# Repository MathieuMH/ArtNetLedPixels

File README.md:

# ArtNetLedPixels
This is a small project to drive up to +4000 WS28xx LED pixels. It is made for a local free family festival called Copacobana. Which takes place in Ghent (Belgium) every year at the end of June.
As a light operator I like to experiment with budget friendly equipment (like WS28xx leds), to create nice moderate effects. Our club stage is mainly for the afterparty.
This project was used to illuminate the logo of the stage.
The board receives it data from a lighting desk, in our situation (Chamsys MQ500). We mainly use the Art-Net protocol since its quite easy to adopt. The output is driven with the FastLED library.

# Required Hardware
The setup consists of the following hardware:
* Teensy 3.1 or 3.2 (there is basicly no difference for this project)
* Wiznet Wiz850io (LAN tranceived based on the WIZ5000)
* Carrierboard (refer to the ArtNet_WS2812B folder, board is drawn in KiCad 5)

# Output
The board has 12 outputs with screw terminal and one with solder terminal at R14.

# Contributors
Mathieu (THIEU.Gent)
Copacobana Festival http://www.copacobana.be

# License
MIT License

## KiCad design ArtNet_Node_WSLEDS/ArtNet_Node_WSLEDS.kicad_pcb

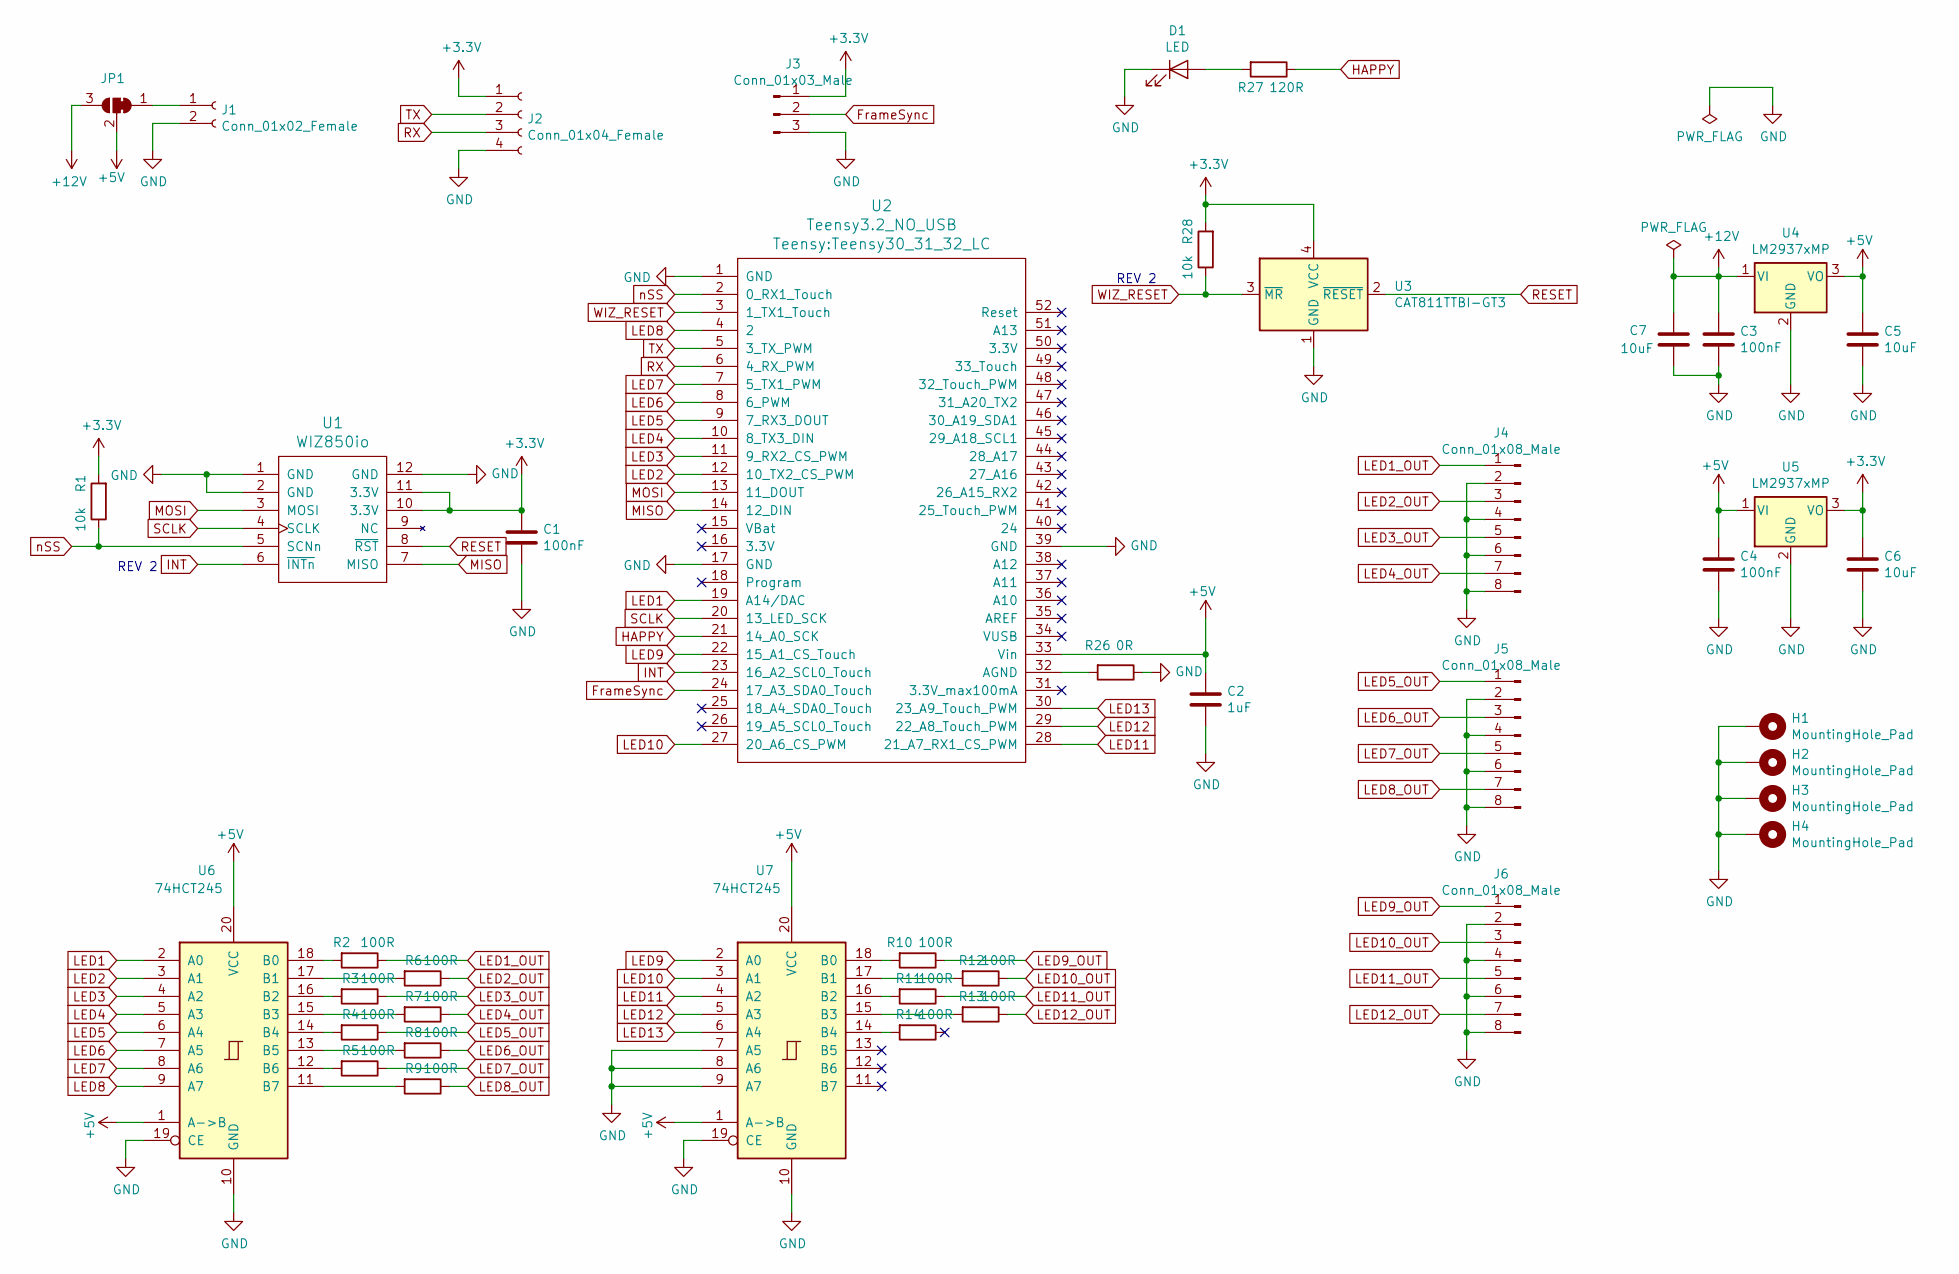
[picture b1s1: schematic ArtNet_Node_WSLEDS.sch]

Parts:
C1, C3, C4: 100nF; C_0805_HandSoldering
C2: 1uF; C_0805_HandSoldering
C5, C6, C7: 10uF; C_0805_HandSoldering
D1: LED; LED_1206_HandSoldering
H1, H2, H3, H4: MountingHole_Pad; MountingHole_4.3mm_M4_Pad
J1: Conn_01x02_Female; TerminalBlock_Phoenix_MPT-2.54mm_2pol
J2: Conn_01x04_Female; TerminalBlock_Phoenix_MPT-2.54mm_4pol
J3: Conn_01x03_Male; TerminalBlock_Phoenix_MPT-2.54mm_3pol
J4, J5, J6: Conn_01x08_Male; TerminalBlock_Phoenix_MPT-2.54mm_8pol
JP1: SolderJumper_3_Bridged12; SolderJumper-3_P1.3mm_Bridged12_Pad1.0x1.5mm_NumberLabels
R1, R28: 10k; R_1206_HandSoldering
R2, R3, R4, R5, R6, R7, R8, R9, R10, R11, R12, R13, R14: 100R; R_1206_HandSoldering
R26: 0R; R_1206_HandSoldering
R27: 120R; R_1206_HandSoldering
U1: WIZ850io
U2: Teensy3.2_NO_USB; Teensy30_31_32_LC
U3: CAT811TTBI-GT3; SOT-143
U4, U5: LM2937xMP; SOT-223-3_TabPin2
U6, U7: 74HCT245; SO-20_12.8x7.5mm_Pitch1.27mm

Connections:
+3V3: C1.1, C6.1, J2.1, J3.1, R1.2, R28.2, U1.10 (3.3V), U1.11 (3.3V), U3.4 (VCC), U5.3 (VO)
+5V: C2.1, C4.1, C5.1, JP1.2 (C), U2.33 (Vin), U4.3 (VO), U5.1 (VI), U6.1 (A->B), U6.20 (VCC), U7.1 (A->B), U7.20 (VCC)
+12V: C3.1, C7.1, JP1.3 (B), U4.1 (VI)
FrameSync: J3.2, U2.24 (17_A3_SDA0_Touch)
GND: C1.2, C2.2, C3.2, C4.2, C5.2, C6.2, C7.2, D1.1 (K), H1.1, H2.1, H3.1, H4.1, J1.2, J2.4, J3.3, J4.2, J4.4, J4.6, J4.8, J5.2, J5.4, J5.6, J5.8, J6.2, J6.4, J6.6, J6.8, R26.1, U1.1 (GND), U1.2 (GND), U1.12 (GND), U2.1 (GND), U2.17 (GND), U2.39 (GND), U3.1 (GND), U4.2 (GND), U5.2 (GND), U6.10 (GND), U6.19 (CE), U7.7 (A5), U7.8 (A6), U7.9 (A7), U7.10 (GND), U7.19 (CE)
HAPPY: R27.1, U2.21 (14_A0_SCK)
INT: U1.6 (~INTn), U2.23 (16_A2_SCL0_Touch)
LED1: U2.19 (A14/DAC), U6.2 (A0)
LED1_OUT: J4.1, R2.1
LED2: U2.12 (10_TX2_CS_PWM), U6.3 (A1)
LED2_OUT: J4.3, R6.1
LED3: U2.11 (9_RX2_CS_PWM), U6.4 (A2)
LED3_OUT: J4.5, R3.1
LED4: U2.10 (8_TX3_DIN), U6.5 (A3)
LED4_OUT: J4.7, R7.1
LED5: U2.9 (7_RX3_DOUT), U6.6 (A4)
LED5_OUT: J5.1, R4.1
LED6: U2.8 (6_PWM), U6.7 (A5)
LED6_OUT: J5.3, R8.1
LED7: U2.7 (5_TX1_PWM), U6.8 (A6)
LED7_OUT: J5.5, R5.1
LED8: U2.4 (2), U6.9 (A7)
LED8_OUT: J5.7, R9.1
LED9: U2.22 (15_A1_CS_Touch), U7.2 (A0)
LED9_OUT: J6.1, R10.1
LED10: U2.27 (20_A6_CS_PWM), U7.3 (A1)
LED10_OUT: J6.3, R12.1
LED11: U2.28 (21_A7_RX1_CS_PWM), U7.4 (A2)
LED11_OUT: J6.5, R11.1
LED12: U2.29 (22_A8_Touch_PWM), U7.5 (A3)
LED12_OUT: J6.7, R13.1
LED13: U2.30 (23_A9_Touch_PWM), U7.6 (A4)
MISO: U1.7 (MISO), U2.14 (12_DIN)
MOSI: U1.3 (MOSI), U2.13 (11_DOUT)
unnamed: D1.2 (A), R27.2
unnamed: J1.1, JP1.1 (A)
unnamed: R2.2, U6.18 (B0)
unnamed: R3.2, U6.16 (B2)
unnamed: R4.2, U6.14 (B4)
unnamed: R5.2, U6.12 (B6)
unnamed: R6.2, U6.17 (B1)
unnamed: R7.2, U6.15 (B3)
unnamed: R8.2, U6.13 (B5)
unnamed: R9.2, U6.11 (B7)
unnamed: R10.2, U7.18 (B0)
unnamed: R11.2, U7.16 (B2)
unnamed: R12.2, U7.17 (B1)
unnamed: R13.2, U7.15 (B3)
unnamed: R14.2, U7.14 (B4)
unnamed: R26.2, U2.32 (AGND)
RESET: U1.8 (~RST), U3.2 (~RESET)
RX: J2.3, U2.6 (4_RX_PWM)
SCLK: U1.4 (SCLK), U2.20 (13_LED_SCK)
TX: J2.2, U2.5 (3_TX_PWM)
WIZ_RESET: R28.1, U2.3 (1_TX1_Touch), U3.3 (~MR)
nSS: R1.1, U1.5 (SCNn), U2.2 (0_RX1_Touch)

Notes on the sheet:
REV 2

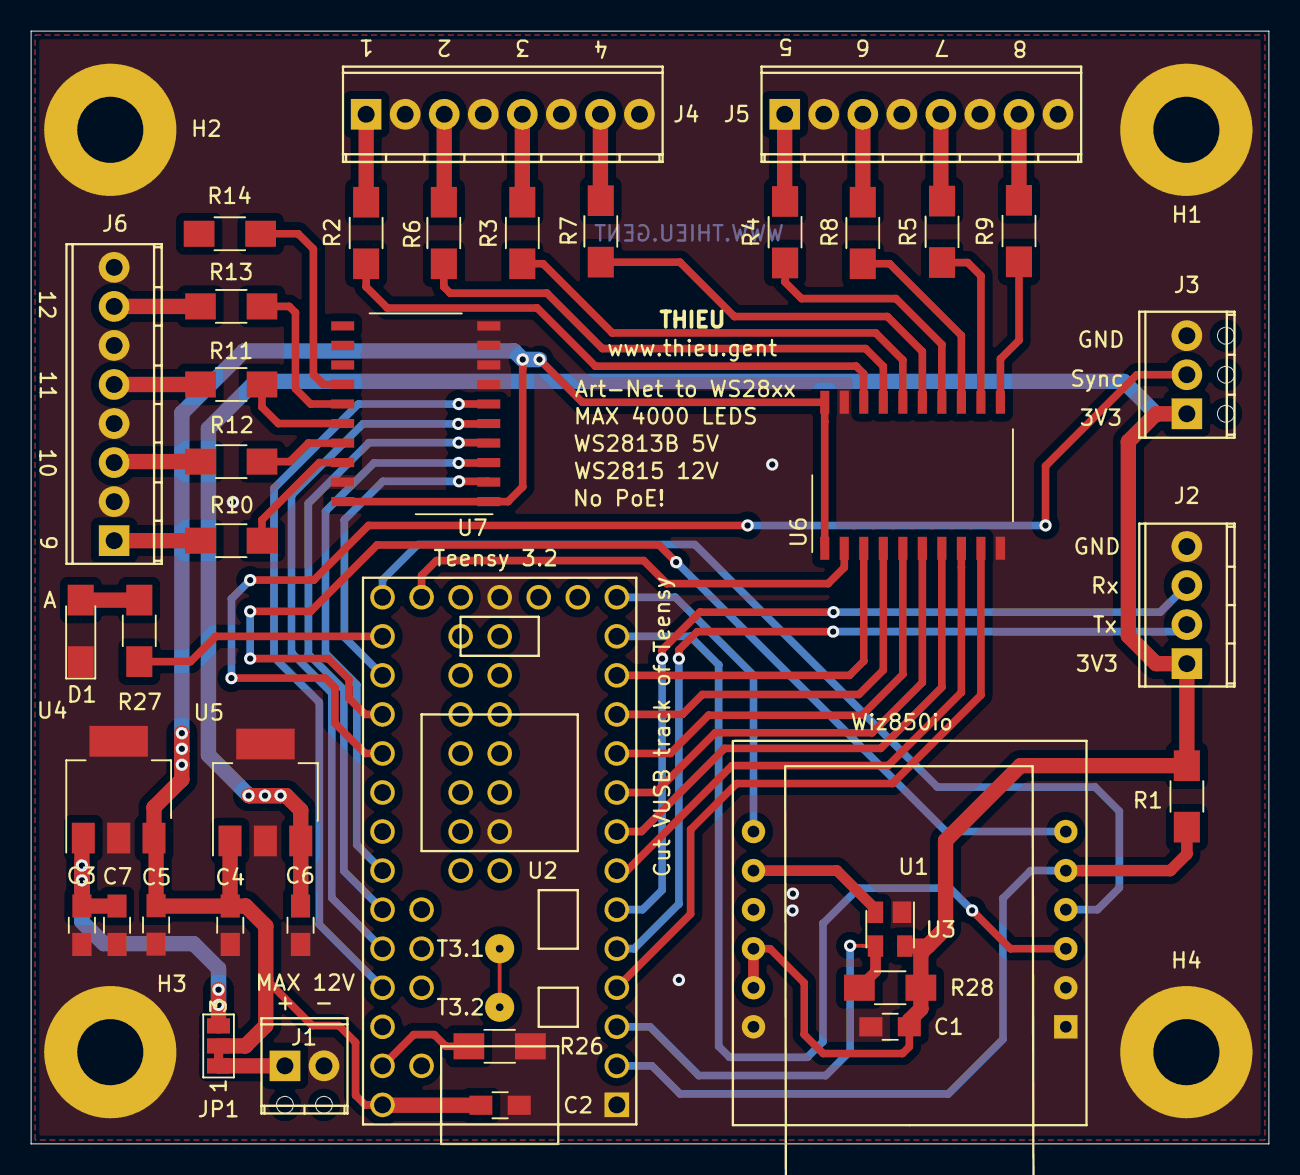
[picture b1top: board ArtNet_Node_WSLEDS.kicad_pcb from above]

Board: 2 copper layers, 80.5 x 72.4 mm, 43 parts (0 on the bottom side), 56 nets.

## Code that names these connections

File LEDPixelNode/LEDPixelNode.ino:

/*H**********************************************************************
* FILENAME :        LEDPixelNode.ino         DESIGN REF: LPXN
*
* DESCRIPTION :
*       This code will receive multiple univers via Art-Net and send
*       it to a multiple WS28xx LED strips.
*
* NOTES :
*       This code is optimized to run on a Teensy 3.x
*       A Wiz850io (or legacy Wiz820io) is used to receive the UPD data.
*       A THIEU designed carrier board to connect everything.
*       
* GIT :
*       https://github.com/MathieuMH/ArtNetLedPixels
*
* AUTHOR :    Mathieu Hebbrecht       START DATE :    22 Januari 2020
*
* CHANGES :
* REF NO  VERSION   DATE        WHO     DETAIL
* LPXN    00.01     22/01/2020  MHT     Initial version
*
* LICENSE :
* MIT license, see the LICENSE file for details
*H*/

#define FASTLED_ALLOW_INTERRUPTS 0
//#define USE_OCTOWS2811
//#include <OctoWS2811.h>
#include <FastLED.h>
#include <Artnet.h>

// --- PIN DEFINITIONS ---
#define LED1          14
#define LED2          10
#define LED3          9
#define LED4          8
#define LED5          7
#define LED6          6
#define LED7          5
#define LED8          2
#define LED9          15
#define LED10         20
#define LED11         21
#define LED12         22
#define LED13         23
#define WIZ_CS        0
#define WIZ_RESET     1
#define WIZ_INT       16
#define HAPPY_LED     13
#define FRAME_SYNC    17
#define UART_RX       4
#define UART_TX       3

// --- GENERIC DEFINITIONS
#define DEBUG                 0       // 0=only operation commands, no debug ; 1=high level debug ; 2=low level debug
#define RELEASE               0       // Significant changes marker (FEATURES)
#define VERSION               1       // Minor change marker (BUG FIXES)
#define HAPPY_PULSE           1000    // HAPPY LED Flash interval
#define NUM_LEDS_PER_STRIP    40      // Number of pixels in each LEDS strip (= output)
#define NUM_LED_STRIPS        1       // Number of strips connected

int inByte = 0;
long previousMillis = 0;
int ledState = HIGH;

// --- FastLED Settings
//CRGB leds[NUM_LEDS_PER_STRIP];
const int numLeds = NUM_LED_STRIPS * NUM_LED_STRIPS;
CRGB leds[numLeds];

// --- Art-Net Settings
Artnet artnet;
int startUniverse = 0;          // Default Artnet universe (in most cases this is 0, but some software require 1 as first)
int previousDataLength = 0;

// --- Network settings
//byte ip[] = {2, 9, 200, 15};
byte broadcast[] = {2, 255, 255, 255};
byte mac[] = {0x72, 0x67, 0xF0, 0xeb, 0x33, 0x30};

void setup()
{
  // - Set pin directions
  //pinMode(HAPPY_LED, OUTPUT);
  pinMode(WIZ_RESET, OUTPUT);
  //pinMode(WIZ_INT, INPUT);
  //pinMode(FRAME_SYNC, INPUT);

    // Port Init
  digitalWrite(WIZ_RESET, LOW);   //Start Wiz850io Reset
  delay(5);
  digitalWrite(WIZ_RESET, HIGH);   //End Wiz850io Reset
  
  // - Serial Init
  Serial.begin(115200);     // For debug and setup
  delay(5);
  Serial.print("LedPixelNode v");
  Serial.print(RELEASE);
  Serial.println("." + VERSION);
  Serial.println( "Compiled: " __DATE__ ", " __TIME__ ", " __VERSION__);
  
  if(DEBUG > 0)
  {  
    while (!Serial) 
    {
      ; // wait for serial port to connect. Needed for native USB port only
    }
    Serial.print("Debug Level is set to: ");
    Serial.println(DEBUG);
  }

  artnet.begin(mac);
  artnet.setBroadcast(broadcast);
  delay(10);

  //Check if Wiz850io is present
  if (Ethernet.hardwareStatus() == EthernetNoHardware) {
    Serial.println("No Wiz850io (or 820io) found. Sorry, can't run without hardware. :(");
    while (true) {
      delay(1); // do nothing, no point running without Ethernet hardware
    }
  }
  if (Ethernet.linkStatus() == LinkOFF) {
    Serial.println("Ethernet cable is not connected.");
  }

    // - FastLed Setup
  FastLED.addLeds<WS2811, LED2>(leds, 0, NUM_LEDS_PER_STRIP);
  //FastLED.addLeds<WS2811, LED2>(leds, NUM_LEDS_PER_STRIP, NUM_LEDS_PER_STRIP);
  //FastLED.addLeds<WS2811, LED3>(leds, NUM_LEDS_PER_STRIP, NUM_LEDS_PER_STRIP);
  //FastLED.addLeds<WS2811, LED4>(leds, NUM_LEDS_PER_STRIP, NUM_LEDS_PER_STRIP);
//  FastLED.addLeds<WS2812B, LED5>(leds, NUM_LEDS_PER_STRIP, NUM_LEDS_PER_STRIP);
//  FastLED.addLeds<WS2812B, LED6>(leds, NUM_LEDS_PER_STRIP, NUM_LEDS_PER_STRIP);
//  FastLED.addLeds<WS2812B, LED7>(leds, NUM_LEDS_PER_STRIP, NUM_LEDS_PER_STRIP);
//  FastLED.addLeds<WS2812B, LED8>(leds, NUM_LEDS_PER_STRIP, NUM_LEDS_PER_STRIP);
//  FastLED.addLeds<WS2812B, LED9>(leds, NUM_LEDS_PER_STRIP, NUM_LEDS_PER_STRIP);
//  FastLED.addLeds<WS2812B, LED10>(leds, NUM_LEDS_PER_STRIP, NUM_LEDS_PER_STRIP);
//  FastLED.addLeds<WS2812B, LED11>(leds, NUM_LEDS_PER_STRIP, NUM_LEDS_PER_STRIP);
//  FastLED.addLeds<WS2812B, LED12>(leds, NUM_LEDS_PER_STRIP, NUM_LEDS_PER_STRIP);
//  FastLED.addLeds<WS2812B, LED13>(leds, NUM_LEDS_PER_STRIP, NUM_LEDS_PER_STRIP);    //Solder pad at R14
  if(DEBUG > 0)
    Serial.println("Enabled 4 FastLED outputs.");

  // - Init test
  startUpTest();

  // this will be called for each packet received
  artnet.setArtDmxCallback(onDmxFrame);
  //artnet.setArtSyncCallback(onSync);
}

void loop()
{
  // *** Art-Net Reading ***
  artnet.read();

//  // *** HAPPY LED ***
//  unsigned long currentMillis = millis();
//  
//  if(currentMillis - previousMillis > HAPPY_PULSE) 
//  {
//    previousMillis = currentMillis;   
//    
//    if (ledState == LOW)
//      ledState = HIGH;
//    else
//      ledState = LOW;
//    
//    digitalWrite(HAPPY_LED, ledState);
//  }
}

void onDmxFrame(uint16_t universe, uint16_t length, uint8_t sequence, uint8_t* data, IPAddress remoteIP)
{
  // read universe and put into the right part of the display buffer
  for (int i = 0; i < length / 3; i++)
  {
    int led = i + (universe - startUniverse) * (previousDataLength / 3);
    if (led < numLeds) {
      leds[i] = CRGB( data[i * 3], data[i * 3 + 1], data[i * 3 + 2]);
      if(DEBUG >= 3)
      {
        Serial.print("onDmxFrame:: LED");
        Serial.print(i*3);
        Serial.print(" R");
        Serial.print(leds[i].red);
        Serial.print(" G");
        Serial.print(leds[i].green);
        Serial.print(" B");
        Serial.println(leds[i].blue);
      }
    }

  }
  previousDataLength = length;

  if(DEBUG == 1)
    Serial.println("F");
  if(DEBUG == 2)
  {
    Serial.print("onDmxFrame:: Frame received. Length: ");
    Serial.println(previousDataLength);
  }
  //In case no sync is receive we do it here. This is assynchronious.
  FastLED.show();
}

void onSync(IPAddress remoteIP) 
{   
    //This is for synchronious output.
    FastLED.show();
    
    if(DEBUG >= 1)
      Serial.println("S");
    if(DEBUG >= 2)
      Serial.println("onSync:: Sync CMD received.");
}

void startUpTest() 
{
  for(int i = 0 ; i < numLeds ; i++)
    leds[i] = CRGB::Red;
  FastLED.show();
  if(DEBUG > 0)
    Serial.println("StartUpTest:: leds::RED");
    
  delay(500);
  for(int i = 0 ; i < numLeds  ; i++)
    leds[i] = CRGB::Green;
  FastLED.show();
  if(DEBUG > 0)
    Serial.println("StartUpTest:: leds::GREEN");
    
  delay(500);
  for(int i = 0 ; i < numLeds  ; i++)
    leds[i] = CRGB::Blue;
  FastLED.show();
  if(DEBUG > 0)
    Serial.println("StartUpTest:: leds::BLUE");
    
  delay(500);
  for(int i = 0 ; i < numLeds  ; i++)
    leds[i] = CRGB::Black;
  FastLED.show();
  if(DEBUG > 0)
    Serial.println("StartUpTest:: END, all leds cleared.");
}

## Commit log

2019-05-08 Initial version
    First (untested release) of PCB files and arduino code. Serial communication not working.
2019-05-22 Update the PCB design;
    Migration to FastLED library (more reliable). And 4 more outputs which makes is 12 in total (+1 if soldered to R14).
    Also change the output driver to 74HCT245. The mosfet solution was not working very on fast speeds.
2019-05-22 Update docs
    Changed to FastLED library.
2019-05-23 Transfer to FastLED lib
    Migration to FastLED lib, also added debuggin information.
2020-01-13 Update sync
    Updates the files. Still not working!
2020-01-14 Update README.md
    corrected a typo.
2020-01-22 Update ArtNet_Node_WSLEDS.sch
    Added a schematic remark
2020-01-27 update
    Did test, receive works flawlessly. Fastled lib is letting me down somehow. check HW to be sure.
